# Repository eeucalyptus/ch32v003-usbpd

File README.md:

# USB-PD on the CH32V003

I'm trying to get USB-PD working on the CH32V003. It doesn't have a dedicated USB-PD module, but I only want to use the chip itself and passive components. I'm using the internal comparator for receiving and a simple voltage divider for transmitting. The timing sensitive part of the firmware is written in assembler, while the rest is written in C. 

The project is still in an early stage and WIP, but I was able to transmit and receive messages. 

I wrote two blog posts about the project:

- [USB PD coding](https://eeucalyptus.net/2023-12-06-usb-pd-1.html)
- [USB PD on the CH32V003](https://eeucalyptus.net/2024-05-13-usb-pd-2.html)

## Setup

The development board can be found in the board directory. The board is a breakout board with the required passive components, a USB-C connector and a high voltage capable voltage regulator. 

The firmware can be built with the provided makefile. It is built upon [ch32v003fun](https://github.com/cnlohr/ch32v003fun) and the toolchain described there.

Build and run via `make flash`.

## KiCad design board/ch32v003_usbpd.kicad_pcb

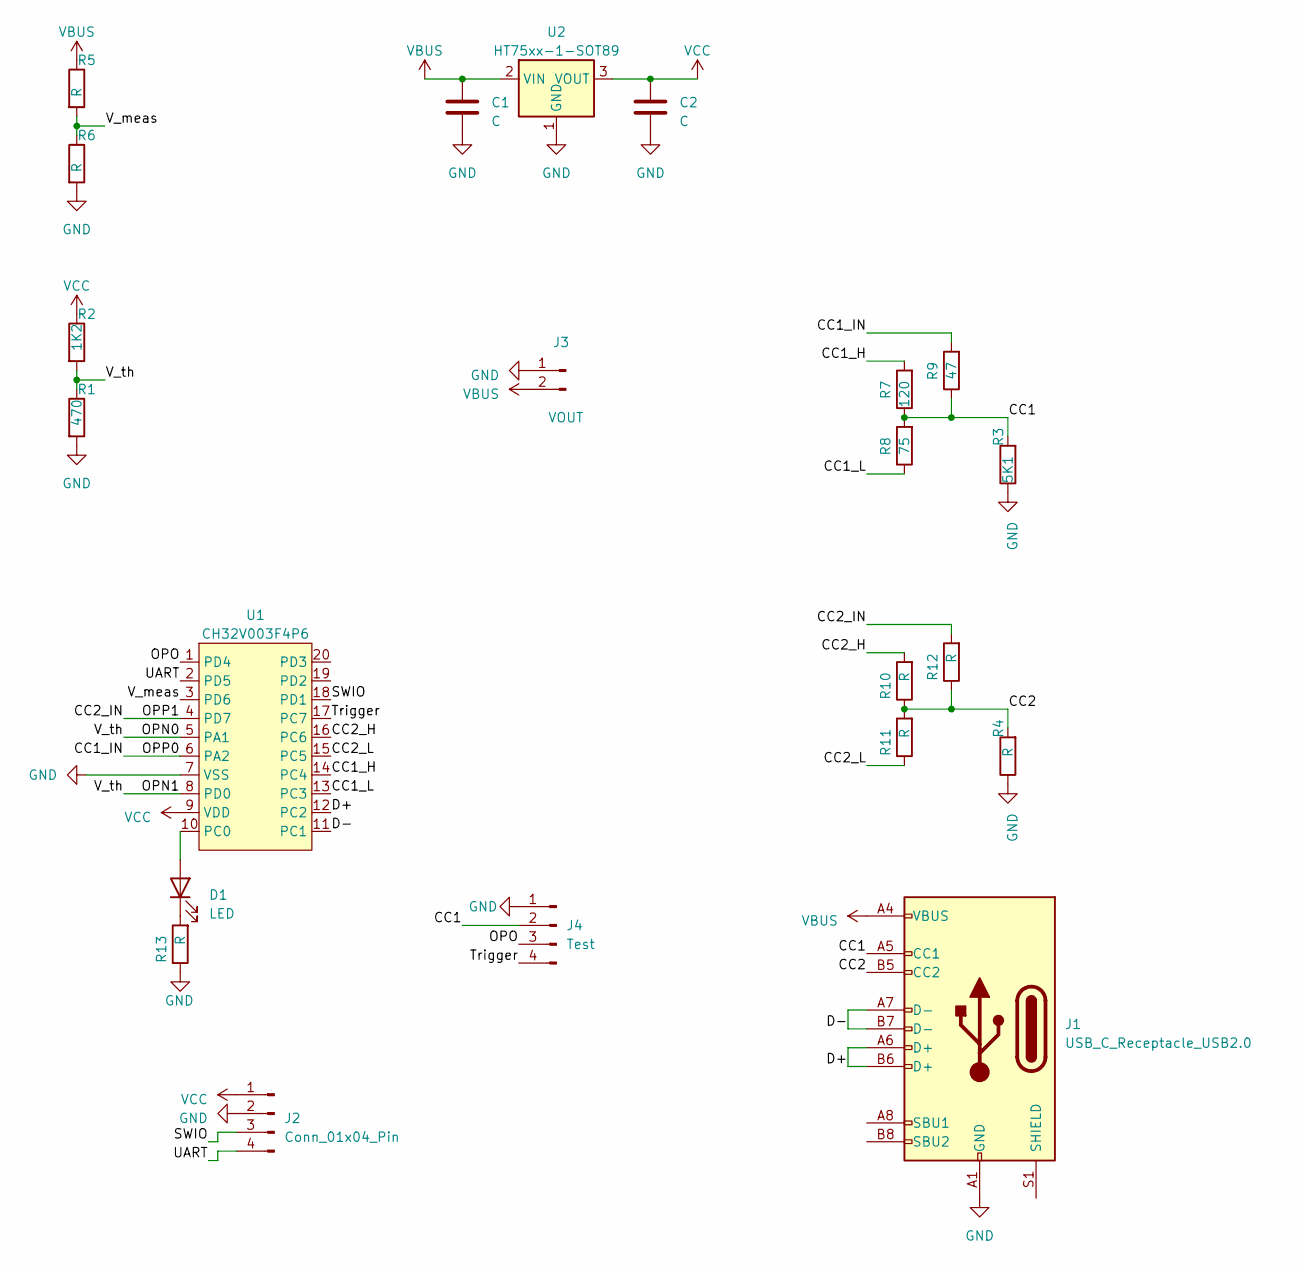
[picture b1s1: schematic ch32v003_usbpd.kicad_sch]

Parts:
C1, C2: C; C_0603_1608Metric
D1: LED; LED_0603_1608Metric
J1: USB_C_Receptacle_USB2.0; USB_C_Receptacle_HRO_TYPE-C-31-M-12
J2: Conn_01x04_Pin; PinHeader_1x04_P2.54mm_Vertical
J3: VOUT; PinHeader_1x02_P2.54mm_Vertical
J4: Test; PinHeader_1x04_P2.54mm_Vertical
R1: 470; R_0805_2012Metric
R2: 1K2; R_0805_2012Metric
R3: 5K1; R_0805_2012Metric
R4, R5, R6, R10, R11, R12, R13: R; R_0805_2012Metric
R7: 120; R_0805_2012Metric
R8: 75; R_0805_2012Metric
R9: 47; R_0805_2012Metric
U1: CH32V003F4P6; TSSOP-20_4.4x6.5mm_P0.65mm
U2: HT75xx-1-SOT89; SOT-89-3

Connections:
/CC1: J1.A5 (CC1), J4.2, R3.2, R7.1, R8.2, R9.1
/CC1_H: R7.2, U1.14 (PC4)
/CC1_IN: R9.2, U1.6 (PA2)
/CC1_L: R8.1, U1.13 (PC3)
/CC2: J1.B5 (CC2), R4.2, R10.1, R11.2, R12.1
/CC2_H: R10.2, U1.16 (PC6)
/CC2_IN: R12.2, U1.4 (PD7)
/CC2_L: R11.1, U1.15 (PC5)
/D+: J1.A6 (D+), J1.B6 (D+), U1.12 (PC2)
/D-: J1.A7 (D-), J1.B7 (D-), U1.11 (PC1)
/OPN0: R1.1, R2.2, U1.5 (PA1), U1.8 (PD0)
/OPO: J4.3, U1.1 (PD4)
/SWIO: J2.3, U1.18 (PD1)
/Trigger: J4.4, U1.17 (PC7)
/UART: J2.4, U1.2 (PD5)
/V_meas: R5.2, R6.1, U1.3 (PD6)
GND: C1.2, C2.2, J1.A1 (GND), J1.A12 (GND), J1.B1 (GND), J1.B12 (GND), J2.2, J3.1, J4.1, R1.2, R3.1, R4.1, R6.2, R13.1, U1.7 (VSS), U2.1 (GND)
unnamed: D1.2 (A), U1.10 (PC0)
unnamed: D1.1 (K), R13.2
VBUS: C1.1, J1.A4 (VBUS), J1.A9 (VBUS), J1.B4 (VBUS), J1.B9 (VBUS), J3.2, R5.1, U2.2 (VIN)
VCC: C2.1, J2.1, R2.1, U1.9 (VDD), U2.3 (VOUT)

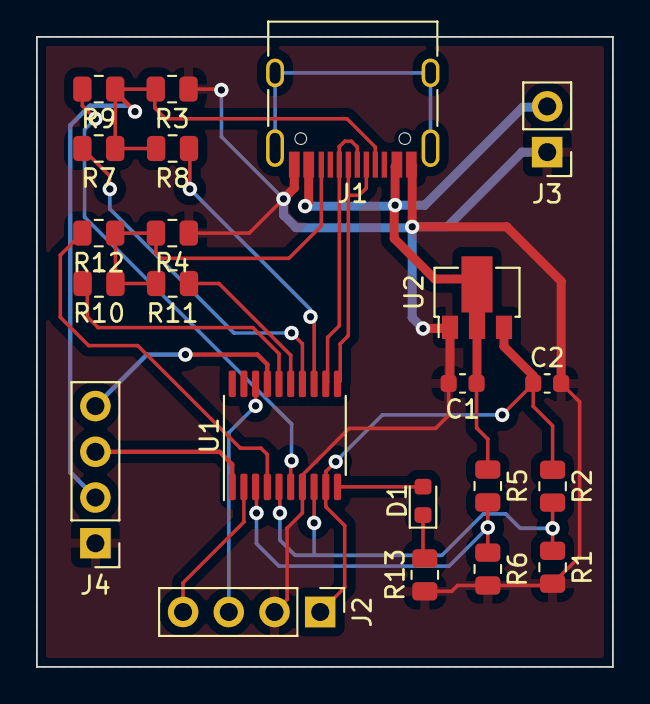
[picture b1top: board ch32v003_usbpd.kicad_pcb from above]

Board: 2 copper layers, 32.0 x 35.0 mm, 22 parts (0 on the bottom side), 21 nets.

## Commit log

2023-12-09 added additional sources to fw build
2023-12-09 fixed decoder bug which emitted a '0' with a prepended high level
2023-12-09 implement bcm encode/decode
2023-12-09 fix kcode order in byte
2023-12-09 improve test sequence and encode/decode actual (dummy) packet
2023-12-09 add firmware build
2023-12-09 Added clangd compile flags for vscode and a readme
2023-12-09 fix typo... I wrote bcm instead of bmc more than 200 times...
2023-12-09 implemented packet decoding from bitstream
2024-02-27 add test board
2024-03-03 Add test points to board
2024-04-07 added prototypes for online encoding and decoding and first decoding draft
2024-04-08 added send draft and renamed read to recv
2024-05-11 somehow working send preamble
2024-05-11 working hard-coded source packet
2024-05-12 add crc and cleanup
2024-05-12 fix bit timing by waiting before the bit, not afterwards
2024-05-12 sending messages with crc generation works
2024-05-12 add custom test message for transmission
2024-05-12 fix readme link
2024-05-13 add blog references to readme
2024-07-02 test message with get srccap and crc working
2024-07-02 incoming preamble can be parsed
